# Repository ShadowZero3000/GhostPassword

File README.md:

# GhostPassword
Android app that will sync with an open source hardware device for two factor authentication, encrypted password storage, and random password generation.

This is a hackathon project, so code quality may not conform to best practices, etc.

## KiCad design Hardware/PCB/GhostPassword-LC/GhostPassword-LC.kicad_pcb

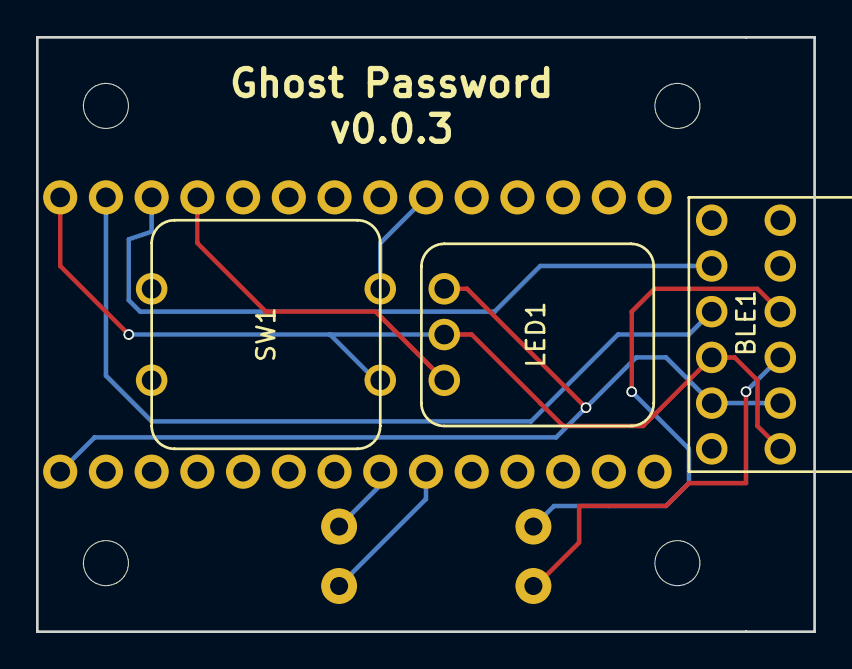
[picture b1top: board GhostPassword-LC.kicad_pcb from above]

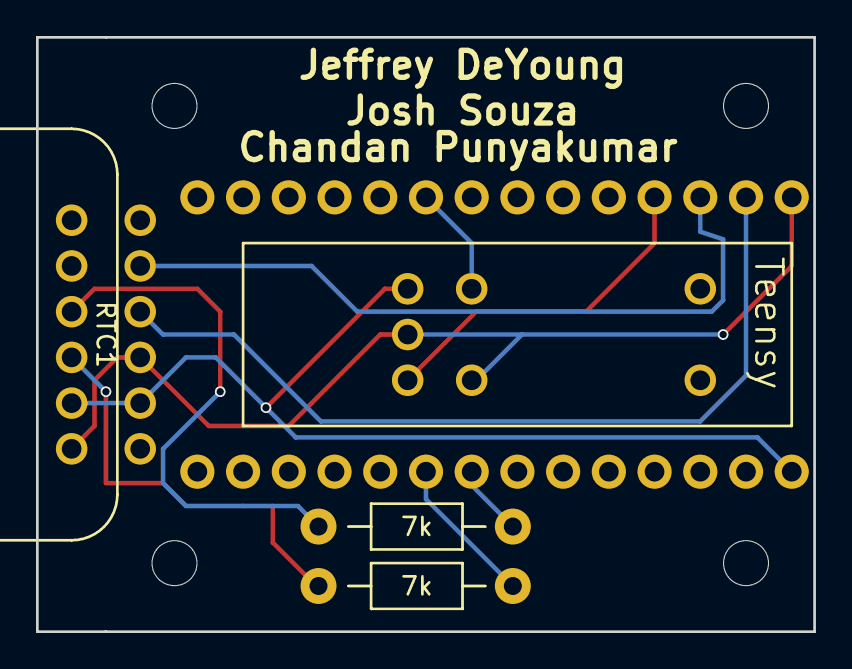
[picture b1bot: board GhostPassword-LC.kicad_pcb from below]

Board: 2 copper layers, 43.2 x 33.0 mm, 7 parts (4 on the bottom side), 10 nets.

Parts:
7k, 7k#2: R_Small; Resistor_Horizontal_RM10mm
BLE1: BlueSmirfHID
LED1: NeoPixel_Jewel
RTC1: DS3231
SW1: SW_PUSH; Tactile_switch
Teensy: Teensy_3.1; Teensy-3.1

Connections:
/BLE-RX-1: BLE1.5, Teensy.1
/BTN-IN: SW1.1, Teensy.7
/GND: BLE1.3, LED1.2, RTC1.1, SW1.2, Teensy.27
/LED-DIN: LED1.3, Teensy.2
/RTC-SCL: 7k.2, RTC1.4
/RTC-SDA: 7k#2.2, RTC1.3
/VCC: BLE1.2, LED1.1, RTC1.2, Teensy.26
unnamed: 7k.1, Teensy.19
unnamed: BLE1.4, Teensy.0
unnamed: 7k#2.1, Teensy.18

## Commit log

2015-10-01 started project structure
2015-10-01 first code
2015-10-01 restarting project structure
2015-10-01 refactor to maven project
2015-10-01 encryption and decryption working
2015-10-01 javadoc
2015-10-01 All the base work done for the Arduino
2015-10-01 Password dao work
2015-10-01 password dao
2015-10-01 work on password service
2015-10-01 added disclaimer to readme
2015-10-01 initial andriod - has 3 basic activities
2015-10-01 more password work
2015-10-01 test and fixes
2015-10-01 more tests, more progress; not sure if they pass or not yet, commiting in case the test botches my box
2015-10-01 added zxing - pushed to save
2015-10-01 lots of progress on the backend
2015-10-01 more tests
2015-10-01 qr camera works
2015-10-01 removed imls and ./idea's
2015-10-01 updated gitignore
2015-10-02 qr code scanner working
2015-10-02 added deps for backend
2015-10-02 added backend to android project
2015-10-02 added ghost image
2015-10-02 some work?
2015-10-02 fixed chandans ghost issues
2015-10-02 renamed old backend stuff; evidently i also updated gitignore (dont recall) and added a pom to make netbeans happy -- everyone else ignore the pom
2015-10-02 More android work
2015-10-02 icons change
2015-10-02 some more progress; added tests back in
2015-10-02 some progress
2015-10-02 whoohoo -- doesn't crash
2015-10-02 major progress
2015-10-02 more progress
2015-10-02 added list
2015-10-02 some progress with chandan
2015-10-02 more work
2015-10-02 changes to the theme
2015-10-02 some cleanup
2015-10-02 cleanup
2015-10-02 more fixes
2015-10-02 cleaned up QR code UI
2015-10-02 try for the grid button layout
2015-10-02 bugfix i think
2015-10-02 stashing it
2015-10-02 hacked for demo
2015-10-02 crud
2015-10-02 gridlayour changes
2015-10-02 removeed .idea
2015-10-02 Final state arduino code
2015-10-13 Updated with descriptions of the pinouts
2015-10-13 Hardware documentation
2015-10-13 Updated with estimated costs
2015-10-13 Let's make the LED not as bright as the sun if it starts up successfully
2015-10-14 Adjusted to enable a 'debug mode'. Nothing will ever print on the serial output unless the button is pressed down during startup. If it powers up while the button is pressed, it enters debug mode, an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
2015-10-20 changes to bluetooth
2015-10-20 Adding exception handling
2015-10-21 Marking sda/scl pinout
2015-10-29 A few tweaks that make the bluetooth communication MUCH faster (nearly instant). Need to discuss as a team.
2015-11-11 added .idea to .gitignore
2015-11-23 Iterating arduino
2015-11-23 Better starting state for the string -> char change
2015-11-23 Updating to a central logging method (to simplify code)
2015-11-23 This works in theory, but reading from EEPROM keeps breaking
2015-11-23 Got the Arduino code working right with an LC
2015-11-24 Committing initial PCB layout (v0.0.3)
2015-11-24 Adding the 3d sketches for the case (SketchUp) As well as the STL files
2015-11-24 Gitignore to clean up the KiCad/Sketchup mess
2015-11-24 Turning off debug mode
2015-11-25 Adding colors for when BT and button actions occur
2015-11-25 Adjust delay after button presses
2017-03-10 I rebuilt the app from the ground up, and it seems to be working
    I'd like to get the OTP codes stored so you can see them in the app as well
2017-05-23 Correct time reference and delete placement
2019-11-26 Not sure what these changes were
2019-11-26 Refactor for newer version
